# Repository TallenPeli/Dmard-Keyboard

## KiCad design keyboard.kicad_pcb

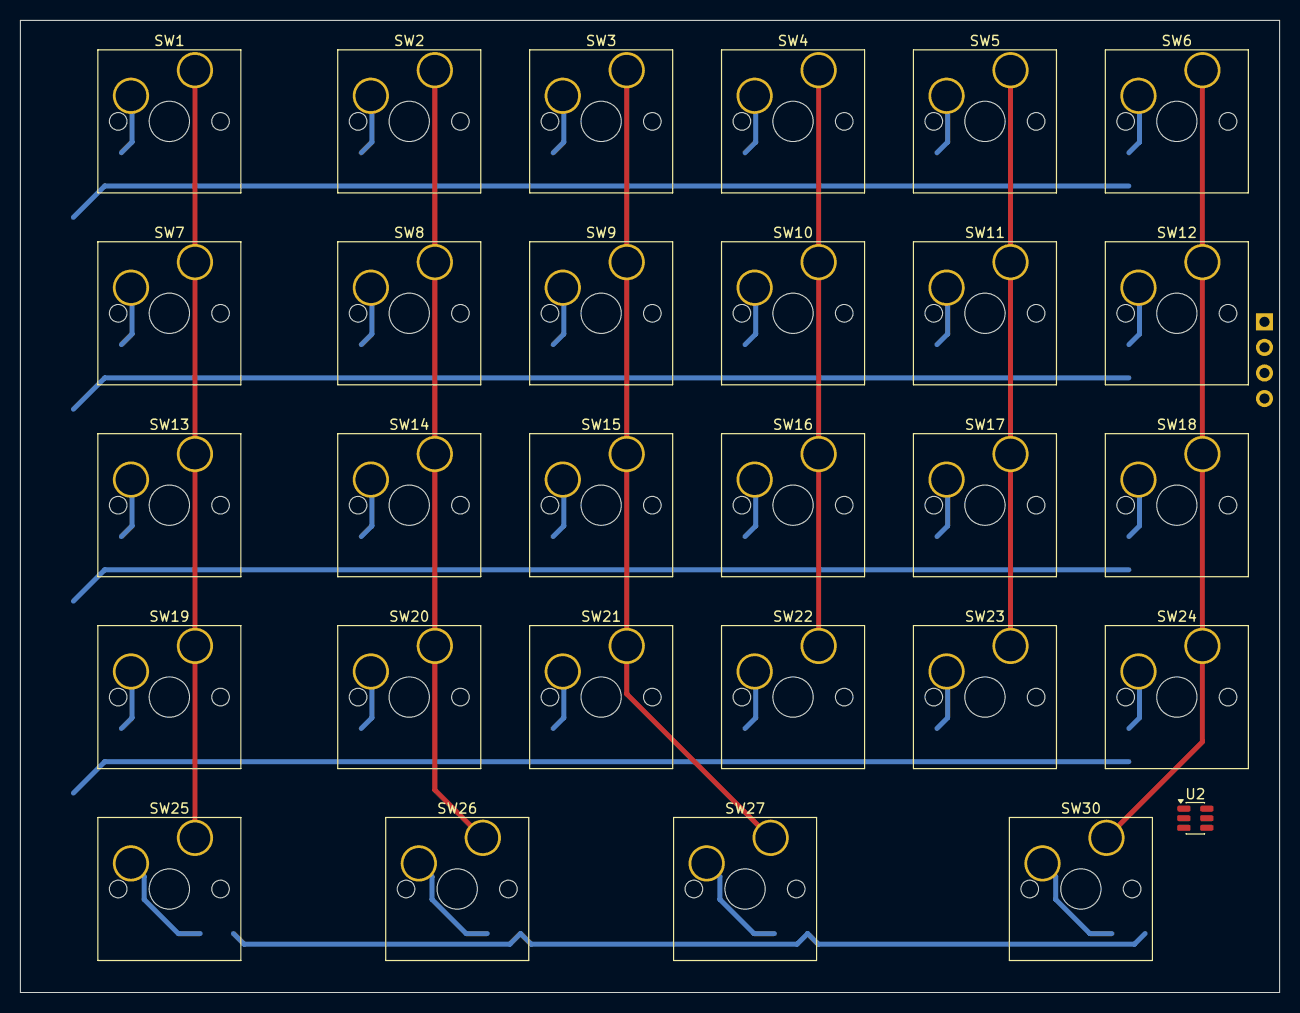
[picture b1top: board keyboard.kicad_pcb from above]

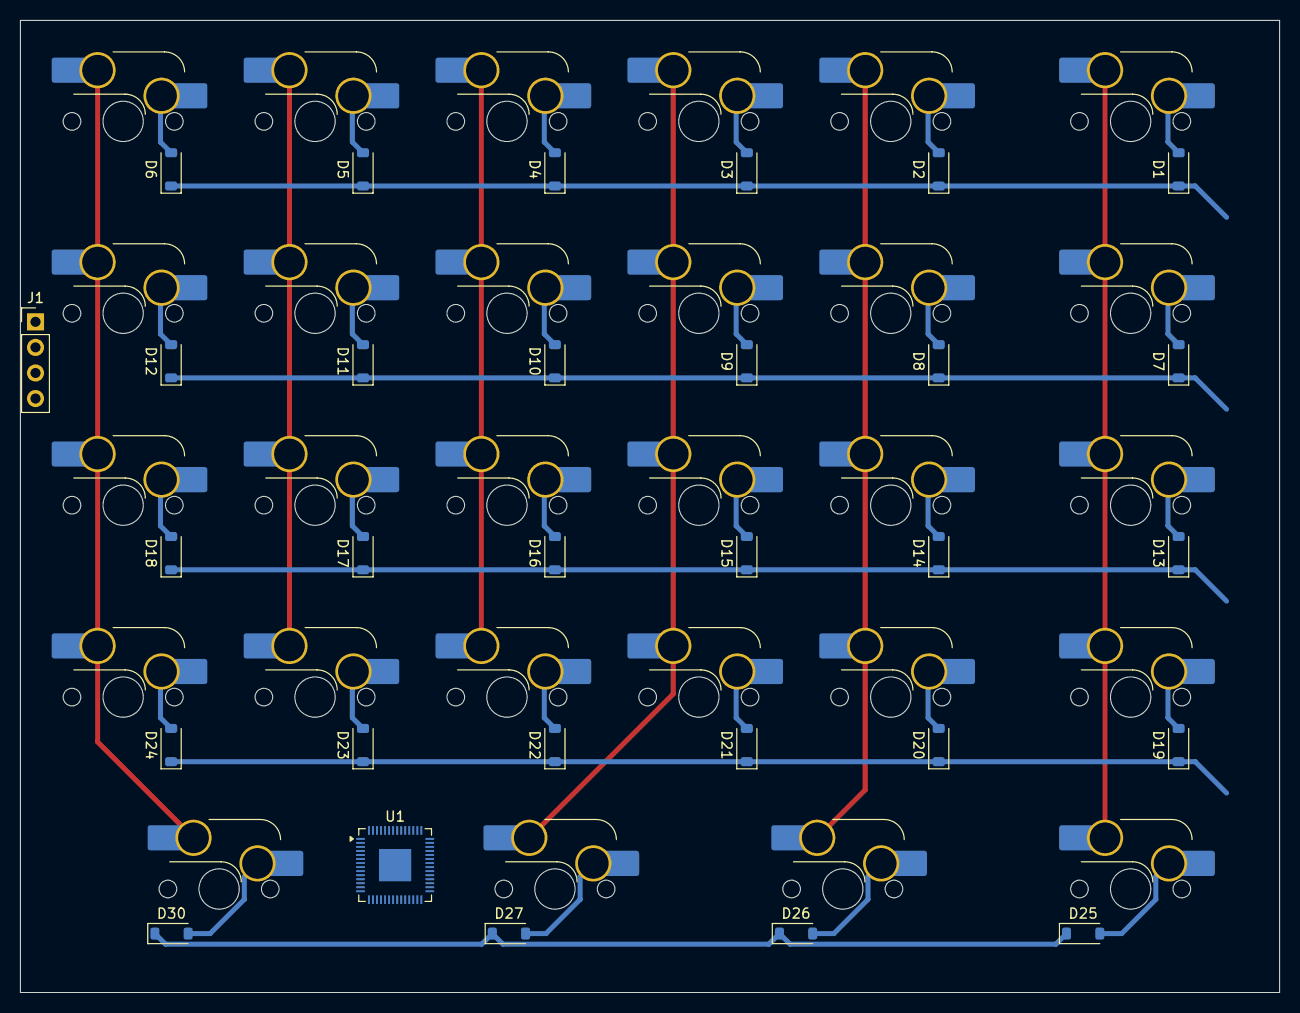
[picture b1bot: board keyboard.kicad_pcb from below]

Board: 2 copper layers, 125.0 x 96.5 mm, 59 parts (30 on the bottom side), 37 nets.

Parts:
D1, D2, D3, D4, D5, D6, D7, D8, D9, D10, D11, D12, D13, D14, D15, D16, D17, D18, D19, D20, D21, D22, D23, D24, D25, D26, D27, D30: D; D_SOD-123
J1: Conn_01x04_Pin; PinHeader_1x04_P2.54mm_Vertical
SW1, SW7, SW13, SW19, SW25, SW26, SW27: SW_Push; SW_Hotswap_Kailh_MX_Plated_1.50u
SW2, SW3, SW4, SW5, SW6, SW8, SW9, SW10, SW11, SW12, SW14, SW15, SW16, SW17, SW18, SW20, SW21, SW22, SW23, SW24: SW_Push; SW_Hotswap_Kailh_MX_Plated_1.00u
SW30: SW_Push; SW_Hotswap_Kailh_MX_Plated_2.00u
U1: RP2040; QFN-56-1EP_7x7mm_P0.4mm_EP3.2x3.2mm
U2: USBLC6-2SC6; SOT-23-6

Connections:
C1: D1.1 (K), D2.1 (K), D3.1 (K), D4.1 (K), D5.1 (K), D6.1 (K), D7.1 (K), D8.1 (K), D9.1 (K), D10.1 (K), D11.1 (K), D12.1 (K), D13.1 (K), D14.1 (K), D15.1 (K), D16.1 (K), D17.1 (K), D18.1 (K), D19.1 (K), D20.1 (K), D21.1 (K), D22.1 (K), D23.1 (K), D24.1 (K), SW1.2, SW2.2, SW3.2, SW4.2, SW5.2, SW6.2, SW7.2, SW8.2, SW9.2, SW10.2, SW11.2, SW12.2, SW13.2, SW14.2, SW15.2, SW16.2, SW17.2, SW18.2, SW19.2, SW20.2, SW21.2, SW22.2, SW23.2, SW24.2, SW25.2, SW26.2, SW27.2, SW30.2, U1.2 (GPIO0), U1.3 (GPIO1), U1.4 (GPIO2), U1.5 (GPIO3), U1.6 (GPIO4), U1.7 (GPIO5), U1.8 (GPIO6), U1.9 (GPIO7), U1.11 (GPIO8), U1.12 (GPIO9)
DM: U1.46 (USB_DM), U2.4 (I/O2)
DP: U1.47 (USB_DP), U2.6 (I/O1)
GND: J1.4, U2.2 (GND)
unnamed: D1.2 (A), SW1.1
unnamed: D2.2 (A), SW2.1
unnamed: D3.2 (A), SW3.1
unnamed: D4.2 (A), SW4.1
unnamed: D5.2 (A), SW5.1
unnamed: D6.2 (A), SW6.1
unnamed: D7.2 (A), SW7.1
unnamed: D8.2 (A), SW8.1
unnamed: D9.2 (A), SW9.1
unnamed: D10.2 (A), SW10.1
unnamed: D11.2 (A), SW11.1
unnamed: D12.2 (A), SW12.1
unnamed: D13.2 (A), SW13.1
unnamed: D14.2 (A), SW14.1
unnamed: D15.2 (A), SW15.1
unnamed: D16.2 (A), SW16.1
unnamed: D17.2 (A), SW17.1
unnamed: D18.2 (A), SW18.1
unnamed: D19.2 (A), SW19.1
unnamed: D20.2 (A), SW20.1
unnamed: D21.2 (A), SW21.1
unnamed: D22.2 (A), SW22.1
unnamed: D23.2 (A), SW23.1
unnamed: D24.2 (A), SW24.1
unnamed: D25.2 (A), SW25.1
unnamed: D26.2 (A), SW26.1
unnamed: D27.2 (A), SW27.1
unnamed: D30.2 (A), SW30.1
unnamed: U1.23 (DVDD), U1.50 (DVDD)
unnamed: U1.1 (IOVDD), U1.10 (IOVDD), U1.22 (IOVDD), U1.33 (IOVDD), U1.42 (IOVDD), U1.49 (IOVDD)
R5: D25.1 (K), D26.1 (K), D27.1 (K), D30.1 (K), U1.13 (GPIO10)
SCL: J1.3, U1.28 (GPIO17)
SDA: J1.2, U1.27 (GPIO16)

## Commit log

2025-10-21 Wired rows and columns and added i2c pinheader
2025-10-24 More wiring for the RP2040
